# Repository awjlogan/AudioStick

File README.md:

# AudioStick

Quality audio carrier board for the Raspberry Pi Zero. A self facilitating media node.

## Description and Getting Started

This board is designed to be used with a Raspberry Pi Zero (W) to turn it into small high quality streaming audio device. It incorporates a soft power switch, which makes it easier to use in normal settings (e.g., don't need to SSH in to shutdown) and prolong the life of the SD card. The AudioStick connects directly to the standard Raspberry Pi 40pin GPIO header.

All design files and source code are under the [_Don't Be A Dick_][dbad-github] license.

### Installation on the Raspberry Pi

From a clean installation of Raspbian, log in to your Raspberry Pi and run the following 3 lines:

```shell
> sudo apt install git
> git clone https://github.com/awjlogan/audiostick.git
> cd ./audiostick
> sudo ./audiostick_setup.sh
```

The `audiostick_setup.sh` script will:
 - Install the PCM5102's configuration in the boot configuration
 - Add the `asound.conf` configuration file
 - Add the power control service
 - Shutdown the Raspberry Pi

When it is complete, you will need to remove and reconnect the power before powering on again.

### Using the AudioStick

 - When the AudioStick is off, there is no power supplied to the Raspberry Pi, so power consumption is minimised.
 - Pressing the button will power on the Raspberry Pi. The power LED will flash until the Raspberry Pi has successfully booted, at which point it will stay on.
 - To turn the AudioStick OFF, press and hold the button for at least one second. The power LED will flash until the Raspberry Pi has safely shutdown. Once the LED returns to pulsing, the Raspberry Pi is completely off and it is safe to remove the power if you wish.

### Raspberry Pi Setup

The AudioStick is intended to be used with something like MPD to allow you to connect up to any speaker (with amplifier) and get access to your local music or streaming services controlled by your phone. There are a lot of good tutorials (REVISIT add some links) available, so I won't reiterate the points here, but here are a few additional things that might be useful:

 - Change the Raspberry Pi's hostname to a meaningful name, for example `livingroompi`. This will also allow you to have multiple AudioSticks on the same network.
 - Configure your NAS (or whatever storage) to mount at boot time in `/etc/fstab`. Be aware that the system might attempt to mount the device before the network is available.
 - Disable the swap file to increase the SD card's life (`sudo apt remove dphys-swapfile`)

## Hardware

### PCB

The PCB was designed using [EAGLE][eagle-web] v9. The *.brd* and *.sch* files are provided, along with a small library of parts (*AudioStick.lbr*). A full bill of materials is provided as an *.ods* file.

### Firmware and flashing the ATtiny13A

The source for the power control microcontroller is provided, and can be compiled with the supplied Makefile. You will need to alter `Makefile` with the programmer that you are using. To compile the firmware:

`> /firmware/make`

The header **J4** on the PCB is a standard Microchip \[Atmel\] 6 pin programming header. Using your compiled firmware (or the precompiled *.hex* file), you can flash the microcontroller with e.g. an Atmel ICE. To flash the microcontroller, run:

`> /firmware/make flash`

## Change Notes

### Version 2.2

 - [x] -ELEC- Change from pogo pads to pin header for AVR ISP.

### Version 2.1

 - [x] -MECH- Mirror RasPi so connectors face Audiostick board.
 - [x] -ELEC- Move LED to PWM output pin for more interesting effects (chicken transistor in case programmer can't drive pin with LED).
 - [x] -ELEC- Remove MOSFET power switch for RasPi. Use inrush inhibitor instead.
 - [x] -ELEC- Downsize RasPi power capacitor.

### Version 2.0

Finalised release PCB, firmware, and RasPi software.

## Datasheets and useful links

- [PCM5102 DAC][pcm5102-datasheet]
- [ATtiny13A][attiny13-datasheet]

[dbad-github]: https://github.com/philsturgeon/dbad
[eagle-web]: https://www.autodesk.com/products/eagle/overview
[pcm5102-datasheet]: http://www.ti.com/product/PCM5102
[attiny13-datasheet]: https://www.microchip.com/wwwproducts/en/ATTINY13A

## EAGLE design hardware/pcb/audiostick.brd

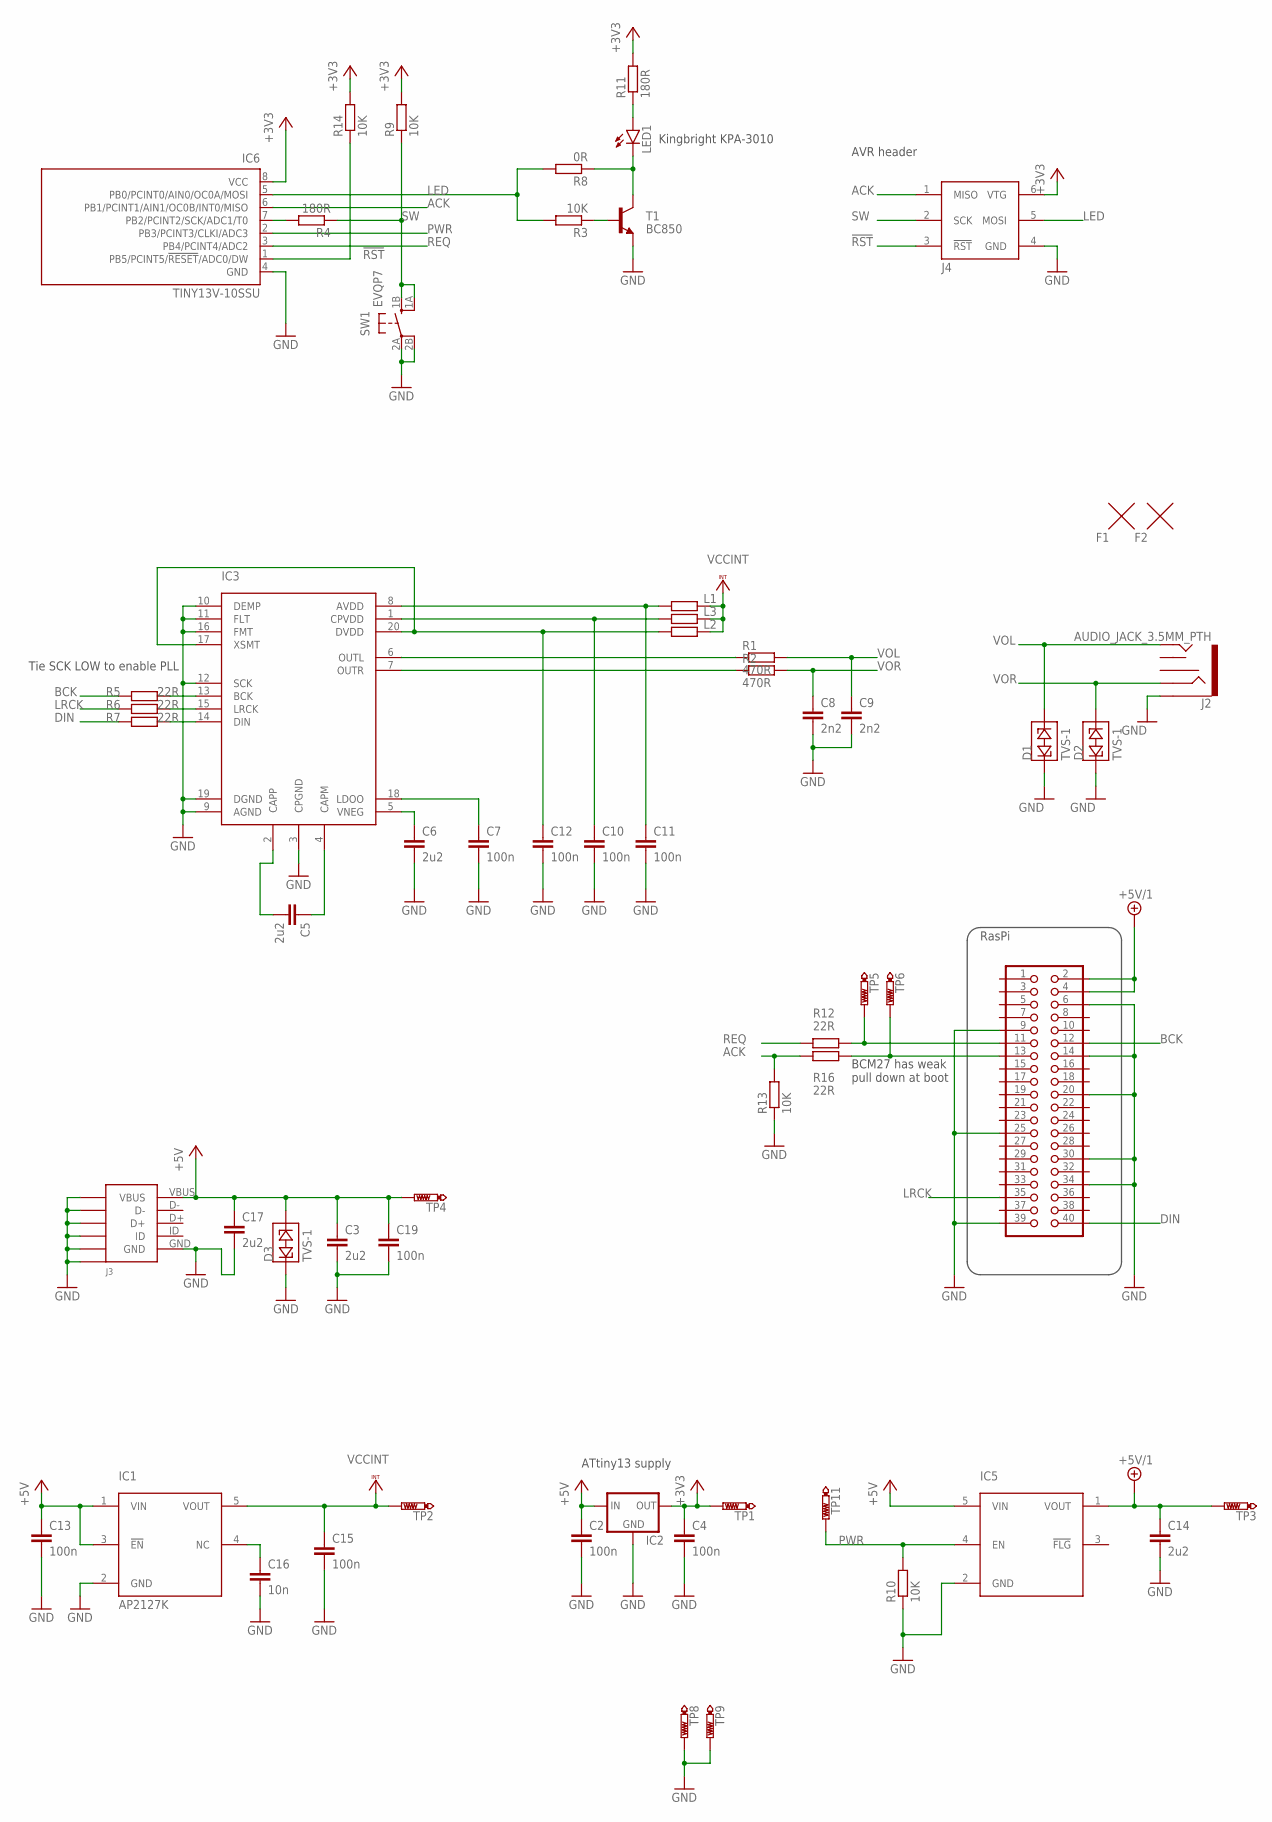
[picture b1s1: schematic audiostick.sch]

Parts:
C2, C4, C7, C10, C11, C12, C13, C15, C19: 100n; C0603
C3, C5, C6, C14, C17: 2u2; C0603
C8, C9: 2n2; C0603
C16: 10n; C0603
D1, D2, D3: TVS-1; R0603
F1, F2: FIDUCIALC2; CIRCLE-1MM-3R
IC1: AP2127K; GHI_SOT23-5
IC2: MCP1700TT; SOT-23
IC3: PCM5102ASW; TSSOP20
IC5: AP22804W5; GHI_SOT23-5
IC6: TINY13V-10SSU; 8S1
J2: AUDIO_JACK_3.5MM_PTH; AUDIO-JACK
J3: USB-B; 1050170001
J4: AVRISP; 2X3-1.27
L1, L2, L3: F; R0603
LED1: LEDLED; KPA-3010
R1, R2: 470R; R0603
R3, R9, R10, R13, R14: 10K; R0603
R4, R11: 180R; R0603
R5, R6, R7, R12, R16: 22R; R0603
R8: 0R; R0603
SW1: EVQP7; EVQP7L
T1: BC850; SOT23
TP1, TP2, TP3, TP4, TP5, TP6, TP8, TP9, TP11: PTR1PAD1-13; P1-13
U$1: RASPIZERO

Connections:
!RST: IC6.1 (PB5/PCINT5/!RESET!/ADC0/DW), J4.3 (!RST), R14.1
+3V3: C4.1, IC2.2 (OUT), IC6.8 (VCC), J4.6 (VTG), R9.2, R11.2, R14.2, TP1.TP
+5V: C2.1, C3.1, C13.1, C17.1, C19.1, D3.2 (3), IC1.1 (VIN), IC1.3 (!EN), IC2.3 (IN), IC5.5 (VIN), J3.VBUS, TP4.TP
+5V/1: C14.1, IC5.1 (VOUT), TP3.TP, U$1.2 (5V), U$1.4 (5V)
ACK: IC6.6 (PB1/PCINT1/AIN1/OC0B/INT0/MISO), J4.1 (MISO), R13.2, R16.1
ACK_IN: R16.2, TP6.TP, U$1.13 (27)
BCK: R5.1, U$1.12 (18)
DIN: R7.1, U$1.40 (21)
GND: C2.2, C3.2, C4.2, C6.2, C7.2, C8.2, C9.2, C10.2, C11.2, C12.2, C13.2, C14.2, C15.2, C16.2, C17.2, C19.2, D1.1, D2.1, D3.1, IC1.2 (GND), IC2.1 (GND), IC3.3 (CPGND), IC3.9 (AGND), IC3.10 (DEMP), IC3.11 (FLT), IC3.12 (SCK), IC3.16 (FMT), IC3.19 (DGND), IC5.2 (GND), IC6.4 (GND), J2.SLEEVE, J3.GND, J3.P$1 (SH1*4), J3.P$2 (SH1*1), J3.P$3 (SH1*2), J3.P$4 (SH1*3), J3.P$10 (SH1*5), J3.P$11 (SH1*6), J4.4 (GND), R10.1, R13.1, SW1.2A, SW1.2B (P1), T1.2 (E), TP8.TP, TP9.TP, U$1.6 (GND), U$1.9 (GND), U$1.14 (GND), U$1.20 (GND), U$1.25 (GND), U$1.30 (GND), U$1.34 (GND), U$1.39 (GND)
LED: IC6.5 (PB0/PCINT0/AIN0/OC0A/MOSI), J4.5 (MOSI), R3.2, R8.2
LRCK: R6.1, U$1.35 (19)
unnamed: C5.1, IC3.4 (CAPM)
unnamed: C5.2, IC3.2 (CAPP)
unnamed: C6.1, IC3.5 (VNEG)
unnamed: C7.1, IC3.18 (LDOO)
unnamed: IC3.6 (OUTL), R1.1
unnamed: R3.1, T1.1 (B)
unnamed: C11.1, IC3.8 (AVDD), L1.1
unnamed: IC3.7 (OUTR), R2.1
unnamed: IC3.13 (BCK), R5.2
unnamed: IC3.15 (LRCK), R6.2
unnamed: IC3.14 (DIN), R7.2
unnamed: C12.1, IC3.17 (XSMT), IC3.20 (DVDD), L2.1
unnamed: C10.1, IC3.1 (CPVDD), L3.1
unnamed: LED1.C, R8.1, T1.3 (C)
unnamed: C16.1, IC1.4 (NC)
unnamed: LED1.A, R11.1
unnamed: IC6.7 (PB2/PCINT2/SCK/ADC1/T0), R4.2
PWR: IC5.4 (EN), IC6.2 (PB3/PCINT3/CLKI/ADC3), R10.2, TP11.TP
REQ: IC6.3 (PB4/PCINT4/ADC2), R12.1
SW: J4.2 (SCK), R4.1, R9.1, SW1.1A (S1), SW1.1B (S)
S_REQ': R12.2, TP5.TP, U$1.11 (17)
VCCINT: C15.1, IC1.5 (VOUT), L1.2, L2.2, L3.2, TP2.TP
VOL: C9.1, D1.2 (3), J2.TIP, R1.2
VOR: C8.1, D2.2 (3), J2.RING, R2.2

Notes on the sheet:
Tie SCK LOW to enable PLL
BCM27 has weak pull down at boot
ATtiny13 supply
Kingbright KPA-3010
AVR header

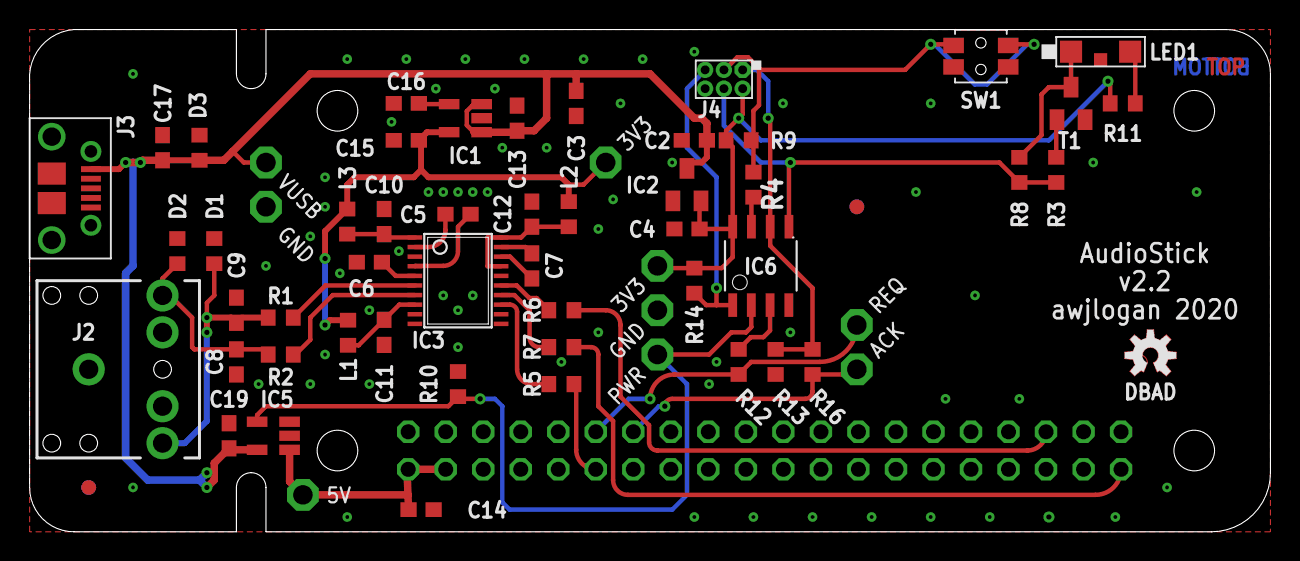
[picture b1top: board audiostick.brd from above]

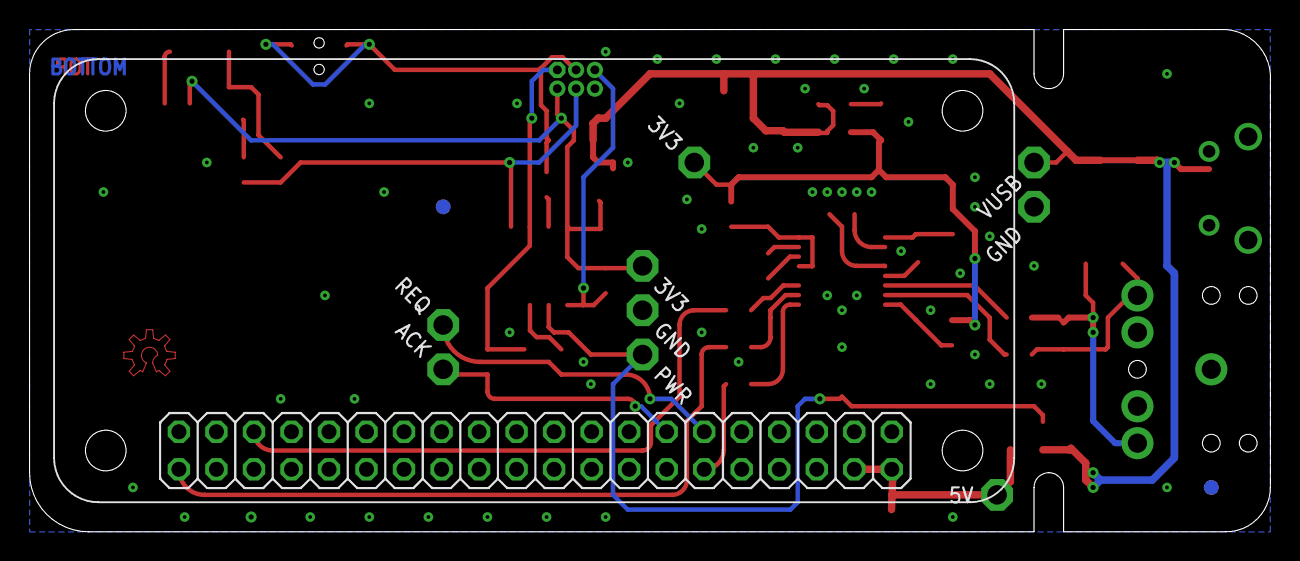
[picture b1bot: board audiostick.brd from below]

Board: 2 copper layers, 84.0 x 34.0 mm, 61 parts (2 on the bottom side), 35 nets.

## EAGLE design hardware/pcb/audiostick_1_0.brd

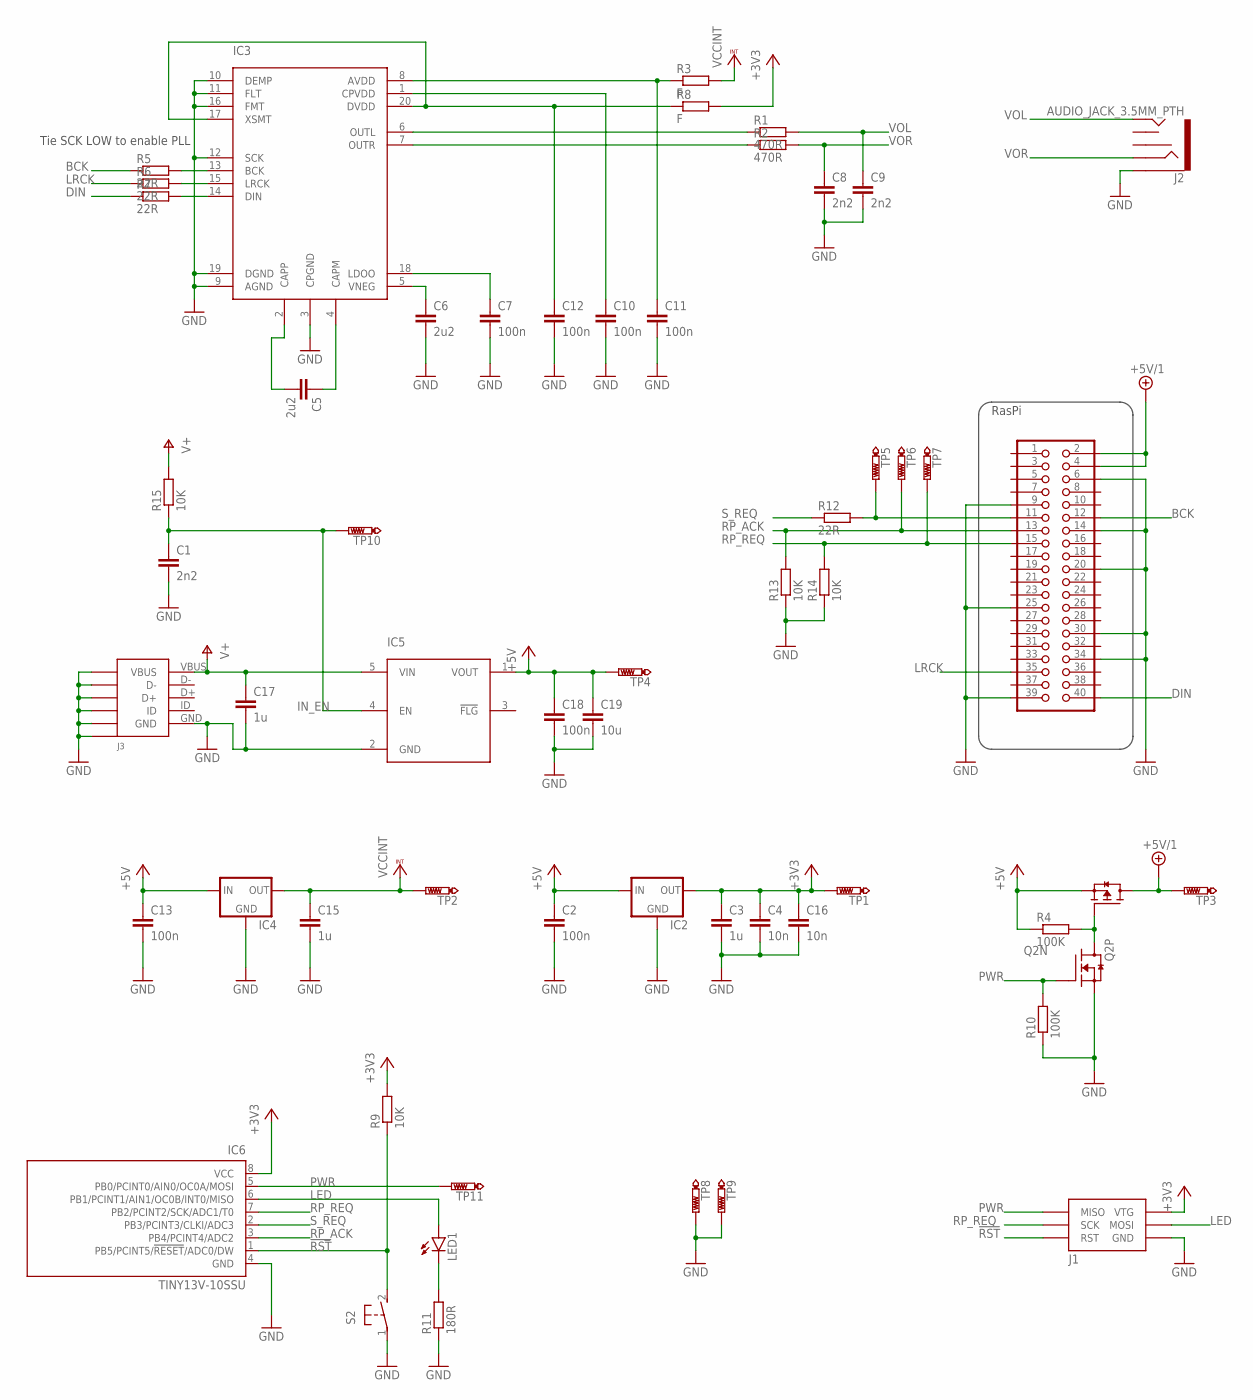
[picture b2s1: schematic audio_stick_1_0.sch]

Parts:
C1, C8, C9: 2n2; C0603
C2, C13: 100n; C0805
C3, C15, C17: 1u; C0805
C4, C16: 10n; C0805
C5, C6: 2u2; C0603
C7, C10, C11, C12, C18: 100n; C0603
C19: 10u; C0805
IC2, IC4: MCP1700TT; SOT-23
IC3: PCM5102ASW; TSSOP20
IC5: AP22804W5; GHI_SOT23-5
IC6: TINY13V-10SSU; 8S1
J1: AVRISP6TH127; 2X3-50MIL
J2: AUDIO_JACK_3.5MM_PTH; AUDIO-JACK
J3: USB-B; 1050170001
LED1: LED3MM
Q2: BSL215; 6TSOP
R1, R2: 470R; R0603
R3, R8: F; R0603
R4, R10: 100K; R0805
R5, R6, R7, R12: 22R; R0603
R9, R13, R14, R15: 10K; R0603
R11: 180R; R0805
S2: 31-XX; B3F-31XX
TP1, TP2, TP3, TP4, TP5, TP6, TP7, TP8, TP9, TP10, TP11: PTR1PAD1-13; P1-13
U$1: RASPIZERO

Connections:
!RST: IC6.1 (PB5/PCINT5/!RESET!/ADC0/DW), J1.5 (RST), R9.1, S2.2 (S)
+3V3: C3.1, C4.1, C16.1, IC2.2 (OUT), IC6.8 (VCC), J1.2 (VTG), R8.2, R9.2, TP1.TP
+5V: C2.1, C13.1, C18.1, C19.1, IC2.3 (IN), IC4.3 (IN), IC5.1 (VOUT), Q2.2 (S), R4.1, TP4.TP
+5V/1: Q2.4 (D), TP3.TP, U$1.2 (5V), U$1.4 (5V)
BCK: R5.1, U$1.12 (18)
DIN: R7.1, U$1.40 (21)
GND: C1.2, C2.2, C3.2, C4.2, C6.2, C7.2, C8.2, C9.2, C10.2, C11.2, C12.2, C13.2, C15.2, C16.2, C17.2, C18.2, C19.2, IC2.1 (GND), IC3.3 (CPGND), IC3.9 (AGND), IC3.10 (DEMP), IC3.11 (FLT), IC3.12 (SCK), IC3.16 (FMT), IC3.19 (DGND), IC4.1 (GND), IC5.2 (GND), IC6.4 (GND), J1.6 (GND), J2.SLEEVE, J3.GND, J3.P$1 (SH1*4), J3.P$2 (SH1*1), J3.P$3 (SH1*2), J3.P$4 (SH1*3), J3.P$10 (SH1*5), J3.P$11 (SH1*6), Q2.5 (S), R10.1, R11.1, R13.1, R14.1, S2.1, TP8.TP, TP9.TP, U$1.6 (GND), U$1.9 (GND), U$1.14 (GND), U$1.20 (GND), U$1.25 (GND), U$1.30 (GND), U$1.34 (GND), U$1.39 (GND)
IN_EN: C1.1, IC5.4 (EN), R15.1, TP10.TP
LED: IC6.6 (PB1/PCINT1/AIN1/OC0B/INT0/MISO), J1.4 (MOSI), LED1.A
LRCK: R6.1, U$1.35 (19)
unnamed: C5.1, IC3.4 (CAPM)
unnamed: C5.2, IC3.2 (CAPP)
unnamed: C6.1, IC3.5 (VNEG)
unnamed: C7.1, IC3.18 (LDOO)
unnamed: IC3.6 (OUTL), R1.1
unnamed: Q2.3 (G), Q2.6 (D), R4.2
unnamed: C10.1, IC3.1 (CPVDD)
unnamed: IC3.7 (OUTR), R2.1
unnamed: IC3.13 (BCK), R5.2
unnamed: IC3.15 (LRCK), R6.2
unnamed: IC3.14 (DIN), R7.2
unnamed: C12.1, IC3.17 (XSMT), IC3.20 (DVDD), R8.1
unnamed: C11.1, IC3.8 (AVDD), R3.1
unnamed: LED1.K (C), R11.2
PWR: IC6.5 (PB0/PCINT0/AIN0/OC0A/MOSI), J1.1 (MISO), Q2.1 (G), R10.2, TP11.TP
RP_ACK: IC6.3 (PB4/PCINT4/ADC2), R13.2, TP6.TP, U$1.13 (27)
RP_REQ: IC6.7 (PB2/PCINT2/SCK/ADC1/T0), J1.3 (SCK), R14.2, TP7.TP, U$1.15 (22)
S_REQ: IC6.2 (PB3/PCINT3/CLKI/ADC3), R12.1
S_REQ': R12.2, TP5.TP, U$1.11 (17)
V+: C17.1, IC5.5 (VIN), J3.VBUS, R15.2
VCCINT: C15.1, IC4.2 (OUT), R3.2, TP2.TP
VOL: C9.1, J2.TIP, R1.2
VOR: C8.1, J2.RING, R2.2

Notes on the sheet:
Tie SCK LOW to enable PLL

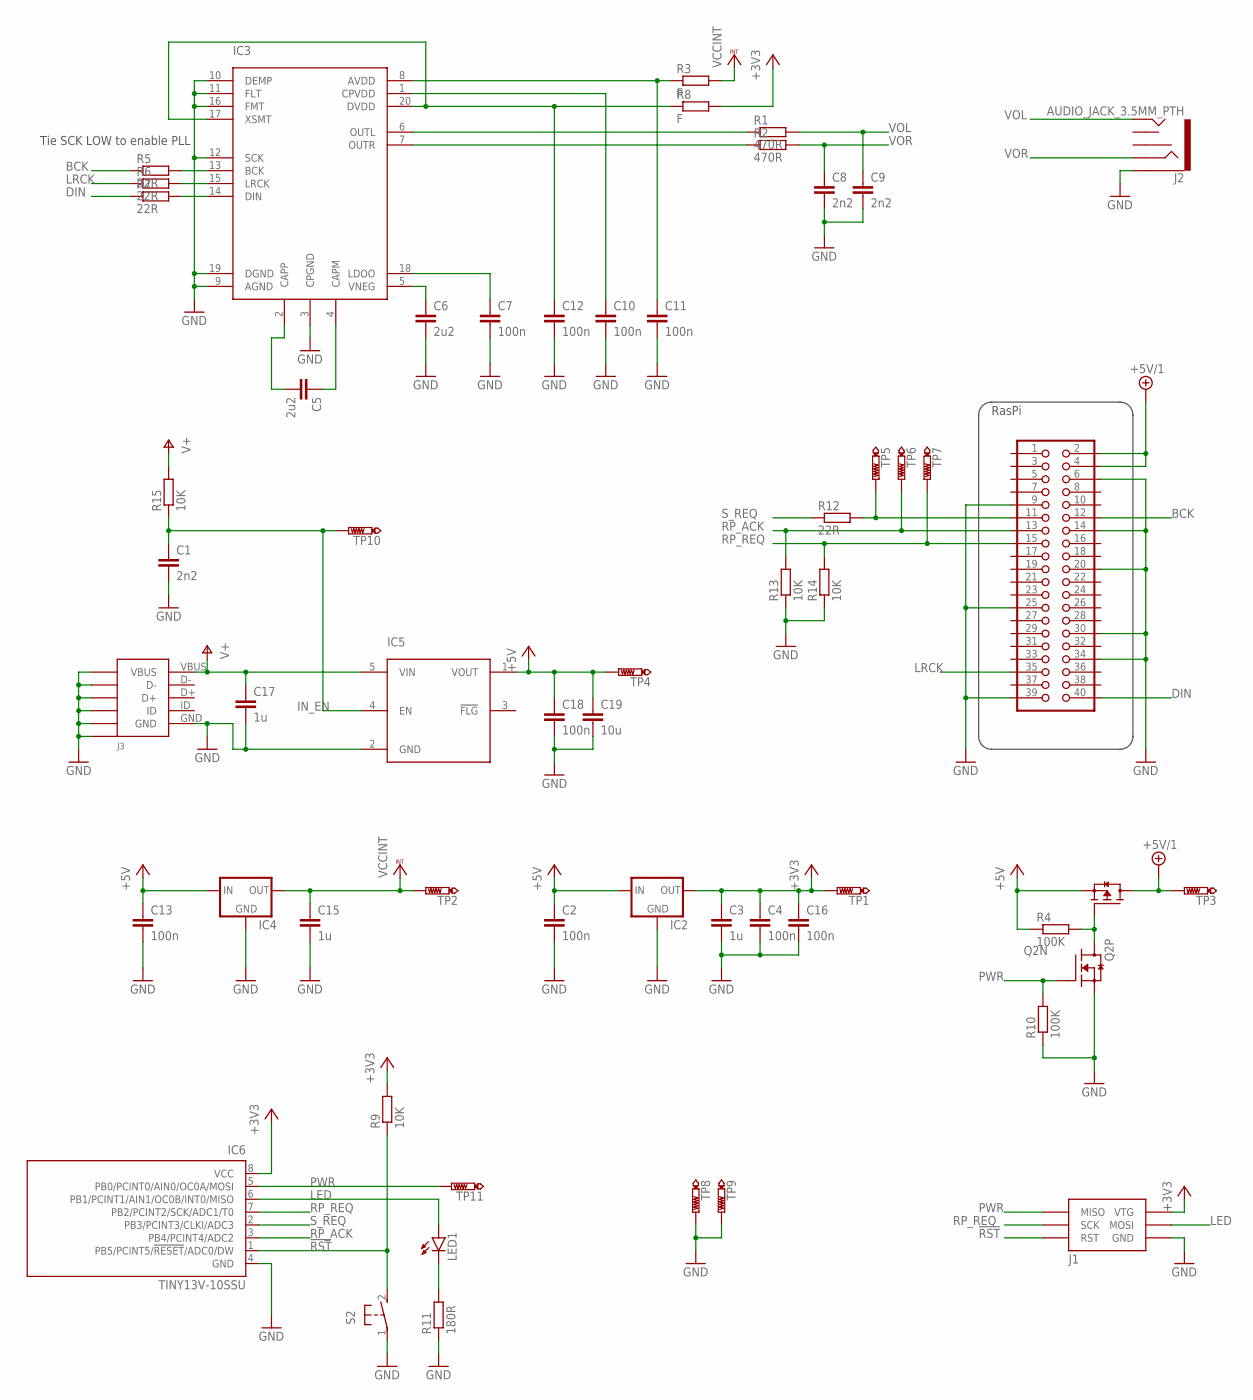
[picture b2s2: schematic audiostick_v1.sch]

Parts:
C1, C8, C9: 2n2; C0603
C2, C4, C13, C16: 100n; C0805
C3, C15, C17: 1u; C0805
C5, C6: 2u2; C0603
C7, C10, C11, C12, C18: 100n; C0603
C19: 10u; C0805
IC2, IC4: MCP1700TT; SOT-23
IC3: PCM5102ASW; TSSOP20
IC5: AP22804W5; GHI_SOT23-5
IC6: TINY13V-10SSU; 8S1
J1: AVRISP6TH127; 2X3-50MIL
J2: AUDIO_JACK_3.5MM_PTH; AUDIO-JACK
J3: USB-B; 1050170001
LED1: LED3MM
Q2: BSL215; 6TSOP
R1, R2: 470R; R0603
R3, R8: F; R0603
R4, R10: 100K; R0805
R5, R6, R7, R12: 22R; R0603
R9, R13, R14, R15: 10K; R0603
R11: 180R; R0805
S2: 31-XX; B3F-31XX
TP1, TP2, TP3, TP4, TP5, TP6, TP7, TP8, TP9, TP10, TP11: PTR1PAD1-13; P1-13
U$1: RASPIZERO

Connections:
!RST: IC6.1 (PB5/PCINT5/!RESET!/ADC0/DW), J1.5 (RST), R9.1, S2.2 (S)
+3V3: C3.1, C4.1, C16.1, IC2.2 (OUT), IC6.8 (VCC), J1.2 (VTG), R8.2, R9.2, TP1.TP
+5V: C2.1, C13.1, C18.1, C19.1, IC2.3 (IN), IC4.3 (IN), IC5.1 (VOUT), Q2.2 (S), R4.1, TP4.TP
+5V/1: Q2.4 (D), TP3.TP, U$1.2 (5V), U$1.4 (5V)
BCK: R5.1, U$1.12 (18)
DIN: R7.1, U$1.40 (21)
GND: C1.2, C2.2, C3.2, C4.2, C6.2, C7.2, C8.2, C9.2, C10.2, C11.2, C12.2, C13.2, C15.2, C16.2, C17.2, C18.2, C19.2, IC2.1 (GND), IC3.3 (CPGND), IC3.9 (AGND), IC3.10 (DEMP), IC3.11 (FLT), IC3.12 (SCK), IC3.16 (FMT), IC3.19 (DGND), IC4.1 (GND), IC5.2 (GND), IC6.4 (GND), J1.6 (GND), J2.SLEEVE, J3.GND, J3.P$1 (SH1*4), J3.P$2 (SH1*1), J3.P$3 (SH1*2), J3.P$4 (SH1*3), J3.P$10 (SH1*5), J3.P$11 (SH1*6), Q2.5 (S), R10.1, R11.1, R13.1, R14.1, S2.1, TP8.TP, TP9.TP, U$1.6 (GND), U$1.9 (GND), U$1.14 (GND), U$1.20 (GND), U$1.25 (GND), U$1.30 (GND), U$1.34 (GND), U$1.39 (GND)
IN_EN: C1.1, IC5.4 (EN), R15.1, TP10.TP
LED: IC6.6 (PB1/PCINT1/AIN1/OC0B/INT0/MISO), J1.4 (MOSI), LED1.A
LRCK: R6.1, U$1.35 (19)
unnamed: C5.1, IC3.4 (CAPM)
unnamed: C5.2, IC3.2 (CAPP)
unnamed: C6.1, IC3.5 (VNEG)
unnamed: C7.1, IC3.18 (LDOO)
unnamed: IC3.6 (OUTL), R1.1
unnamed: Q2.3 (G), Q2.6 (D), R4.2
unnamed: C10.1, IC3.1 (CPVDD)
unnamed: IC3.7 (OUTR), R2.1
unnamed: IC3.13 (BCK), R5.2
unnamed: IC3.15 (LRCK), R6.2
unnamed: IC3.14 (DIN), R7.2
unnamed: C12.1, IC3.17 (XSMT), IC3.20 (DVDD), R8.1
unnamed: C11.1, IC3.8 (AVDD), R3.1
unnamed: LED1.K (C), R11.2
PWR: IC6.5 (PB0/PCINT0/AIN0/OC0A/MOSI), J1.1 (MISO), Q2.1 (G), R10.2, TP11.TP
RP_ACK: IC6.3 (PB4/PCINT4/ADC2), R13.2, TP6.TP, U$1.13 (27)
RP_REQ: IC6.7 (PB2/PCINT2/SCK/ADC1/T0), J1.3 (SCK), R14.2, TP7.TP, U$1.15 (22)
S_REQ: IC6.2 (PB3/PCINT3/CLKI/ADC3), R12.1
S_REQ': R12.2, TP5.TP, U$1.11 (17)
V+: C17.1, IC5.5 (VIN), J3.VBUS, R15.2
VCCINT: C15.1, IC4.2 (OUT), R3.2, TP2.TP
VOL: C9.1, J2.TIP, R1.2
VOR: C8.1, J2.RING, R2.2

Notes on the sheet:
Tie SCK LOW to enable PLL

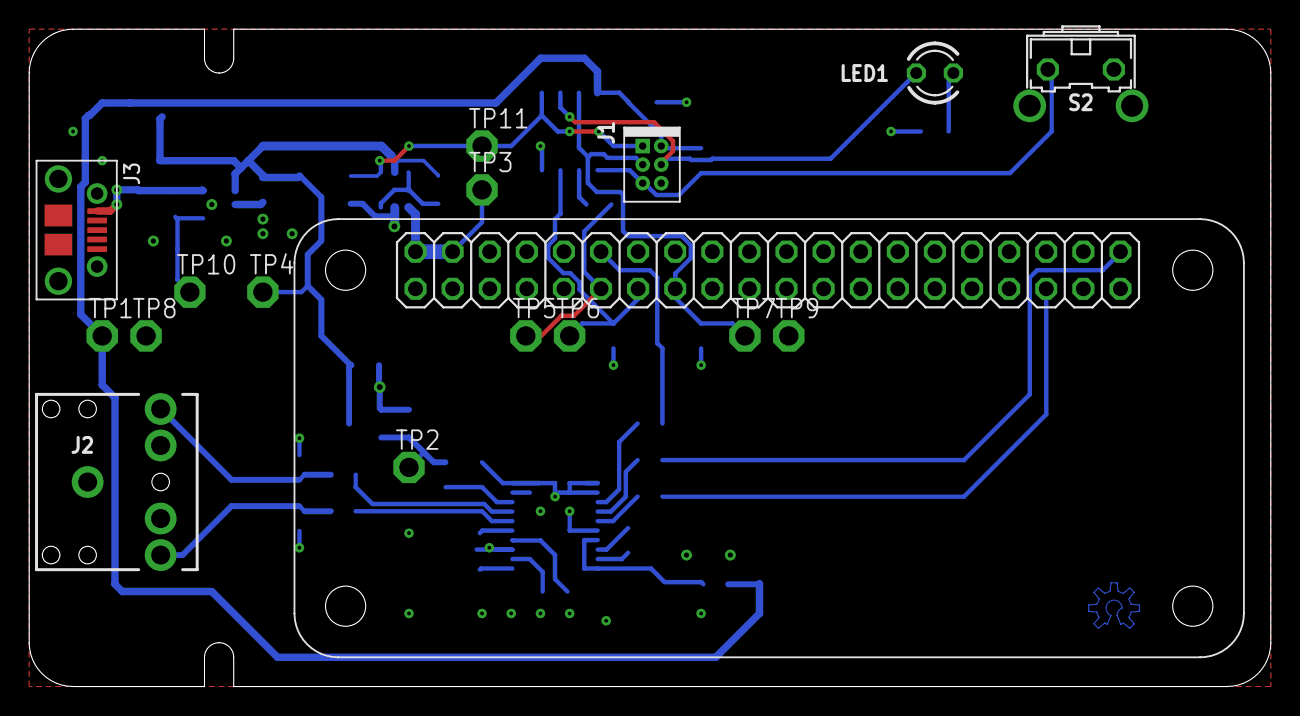
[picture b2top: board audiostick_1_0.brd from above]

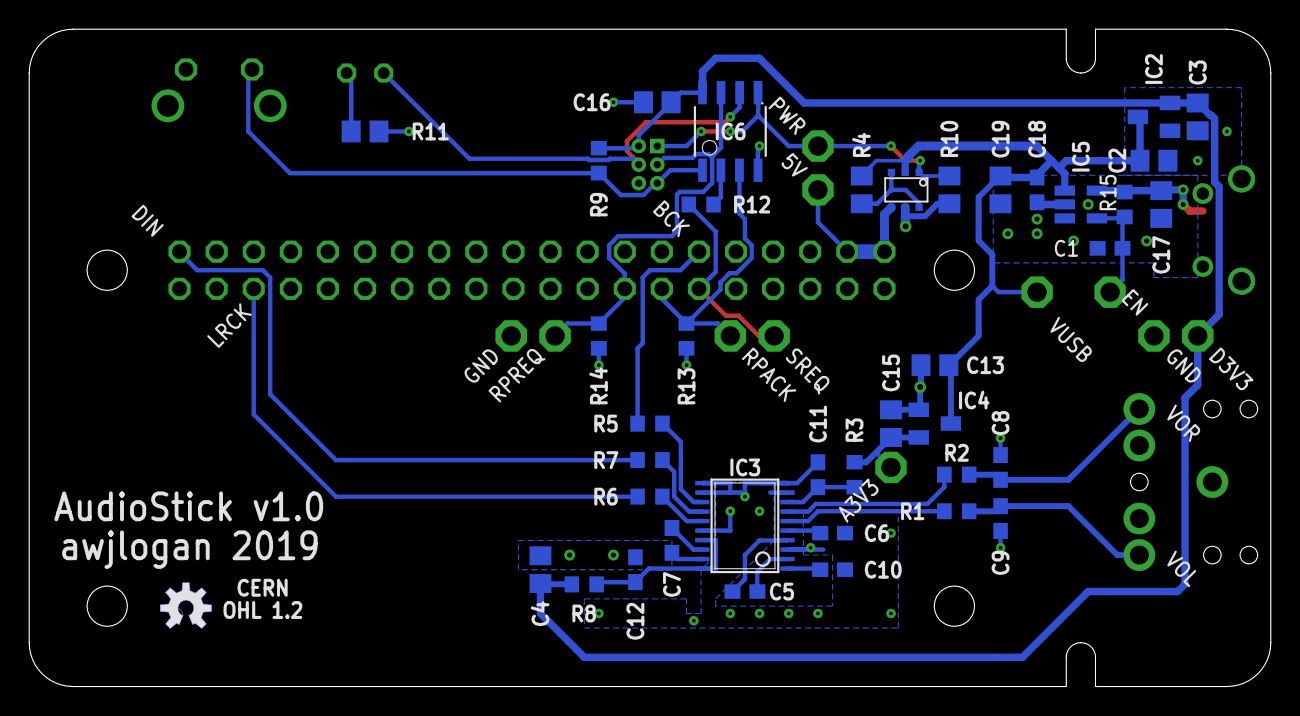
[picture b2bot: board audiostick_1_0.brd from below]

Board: 2 copper layers, 85.0 x 45.0 mm, 56 parts (39 on the bottom side), 33 nets.

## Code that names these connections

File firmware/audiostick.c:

/*

Copyright 2019 Angus Logan

Permission is hereby granted, free of charge, to any person obtaining a copy of
this software and associated documentation files (the "Software"), to deal in
the Software without restriction, including without limitation the rights to
use, copy, modify, merge, publish, distribute, sublicense, and/or sell copies
of the Software, and to permit persons to whom the Software is furnished to
do so, subject to the following conditions:

The above copyright notice and this permission notice shall be included in all
copies or substantial portions of the Software.

THE SOFTWARE IS PROVIDED "AS IS", WITHOUT WARRANTY OF ANY KIND, EXPRESS OR
IMPLIED, INCLUDING BUT NOT LIMITED TO THE WARRANTIES OF MERCHANTABILITY,
FITNESS FOR A PARTICULAR PURPOSE AND NONINFRINGEMENT. IN NO EVENT SHALL THE
AUTHORS OR COPYRIGHT HOLDERS BE LIABLE FOR ANY CLAIM, DAMAGES OR OTHER
LIABILITY, WHETHER IN AN ACTION OF CONTRACT, TORT OR OTHERWISE, ARISING FROM,
OUT OF OR IN CONNECTION WITH THE SOFTWARE OR THE USE OR OTHER DEALINGS IN THE
SOFTWARE.

 * Author:  Angus Logan
 * Version: 2.0
 * Date:    January 2020
 * Target:  Microchip [Atmel] ATtiny13A
 *
 * Physical <-> logical pin mapping
 *
 * Package: SOIC8/DIP8
 * Physical     Function        Logical     i/o
 *----------------------------------------------
 *  1           !RST            PB5         -
 *  2           PWR             PB3         o
 *  3           LED             PB4         o
 *  4           < GND >                     -
 *  5           REQ             PB0         o
 *  6           ACK             PB1         i
 *  7           SW              PB2         i
 *  8           < VDD >                     -
 *
 */

#include <avr/io.h>
#include <avr/interrupt.h>
#include <avr/sleep.h>

#include "audiostick.h"

static inline void setup(void);

ISR (TIM0_OVF_vect) {
    // Reset for idle interrupt wakeup
    TCNT0 = TMR0_VAL;
}

int main(void)
{
    /* Switch handler */
    const uint8_t SW_OPEN = 0xFFU; // Switch goes to ground
    const uint8_t SW_CLOSED = 0x0U;
    uint8_t sw_state = SW_OPEN;
    sw_t sw_curr = OPEN;
    sw_t sw_last = OPEN;
    uint8_t was_pressed = 0x0U;

    /* Timers */
    uint16_t rst_assert = 0x0U;  // timer for reset button
    uint16_t wdt_assert = 0x0U;  // timer to catch a hang in a state
    uint8_t wdt_overflow = 0x0U;

    /*  FSM
        From cold power on, start in ON - no software required on RPi
    */
    power_fsm_t power_fsm = ON;
    power_fsm_t power_fsm_nxt = ON;
    uint8_t rp_ack = 0x0U;

    /* Driven outputs */
    uint8_t portb_nxt;
    uint8_t flash_val = NORM_VAL;
    uint8_t flash_count = 0x0U;

    /* Forever */
    setup();

    for (;;) {

        /* Debounce switch
           Shift all left, then add current to LSB
            -> compare again CLOSED/OPEN (depending on pullup/down)
        */
        sw_state <<= 1;
        if (PINB & (1U<<SW)) sw_state++;
        if (sw_state == SW_CLOSED) sw_curr = CLOSED;
        else if (sw_state == SW_OPEN) sw_curr = OPEN;

        /* Reused conditions */
        was_pressed = (sw_curr == CLOSED) && (sw_last == OPEN);
        wdt_overflow = (wdt_assert > TIMEOUT_VAL);
        rp_ack = (PINB & (1U<<ACK));

        // update FSM
        switch (power_fsm) {
        case OFF:
            if (was_pressed) power_fsm_nxt = START_REQ;
            break;
        case START_REQ:
            if (wdt_overflow) power_fsm_nxt = ERROR;
            else if (rp_ack) power_fsm_nxt = START_ACK;
            break;
        case START_ACK:
            if (wdt_overflow) power_fsm_nxt = ERROR;
            else if (!rp_ack) power_fsm_nxt = ON;
            break;
        case ON:
            if (was_pressed) power_fsm_nxt = SHUT_REQ;
            // request to shutdown from RPi
            else if (PINB & (1U<<REQ)) power_fsm_nxt = SHUT_REQ;
            break;
        case SHUT_REQ:
            if (wdt_overflow) power_fsm_nxt = ERROR;
            else if (rp_ack) power_fsm_nxt = SHUT_ACK;
            break;
        case SHUT_ACK:
            if (wdt_overflow) power_fsm_nxt = ERROR;
            else if (!rp_ack) power_fsm_nxt = OFF;
            break;
        case ERROR:
            break;
        }

        /* Update the watchdog timer */
        if (power_fsm != power_fsm_nxt) wdt_assert = 0x0U;
        else wdt_assert++;

        /* Check for reset */
        if ((sw_curr == CLOSED) && (sw_last == CLOSED)) rst_assert++;
        else rst_assert = 0x0U;
        if (rst_assert > RST_VAL) power_fsm_nxt = OFF;

        // Update FSM state
        power_fsm = power_fsm_nxt;
        sw_last = sw_curr;

        /* Drive FSM outputs */
        portb_nxt = PORTB;

        // Flash by default, exceptions ON/OFF are handled in FSM
        flash_count++;
        if (flash_count > flash_val) {
            portb_nxt ^= (1U<<LED);
            flash_count = 0x0U;
        }

        switch (power_fsm) {
        case OFF:
            flash_val = NORM_VAL;
            portb_nxt &= ~(1U<<LED) & ~(1U<<PWR);  // LED & power off
            break;
        case START_REQ:
            portb_nxt |= (1U<<PWR) | (1U<<REQ);  // power on and assert REQ
            break;
        case START_ACK:
            portb_nxt &= ~(1U<<REQ);  // Clear REQ
            break;
        case ON:
            portb_nxt |= (1U<<LED);  // LED on
            break;
        case SHUT_REQ:
            portb_nxt |= (1U<<REQ);  // Assert REQ
            break;
        case SHUT_ACK:
            portb_nxt &= ~(1U<<REQ);  // Clear REQ
            break;
        case ERROR:
            flash_val = ERR_VAL;
            break;
        }
        PORTB = portb_nxt;

        // Sleep and wait for timer0 interrupt
        sleep_enable();
        sleep_cpu();
        sleep_disable();
    }
}

static inline void setup(void) {
    /* Clocking: default */
    /* Interrupts: default */

    /* Timer0 */
    /* Overflow every INT_PER ms */
    TCCR0B = (1U<<CS01) | (1U<<CS00);  // clk / 64
    TIMSK0 = (1U<<TOIE0);

    /* Port B: */
    MCUCR = (1U<<PUD);  // disable pull ups
    // Configure outputs
    DDRB = (1U<<DDB0) | (1U<<DDB3) | (1U<<DDB4);

    /* Power reduction */
    PRR = (1U<<PRADC);  // ADC off
    ACSR = (1U<<ACD);  // analog comparator off
}

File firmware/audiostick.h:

/*

Copyright 2019 Angus Logan

Permission is hereby granted, free of charge, to any person obtaining a copy of
this software and associated documentation files (the "Software"), to deal in
the Software without restriction, including without limitation the rights to
use, copy, modify, merge, publish, distribute, sublicense, and/or sell copies
of the Software, and to permit persons to whom the Software is furnished to
do so, subject to the following conditions:

The above copyright notice and this permission notice shall be included in all
copies or substantial portions of the Software.

THE SOFTWARE IS PROVIDED "AS IS", WITHOUT WARRANTY OF ANY KIND, EXPRESS OR
IMPLIED, INCLUDING BUT NOT LIMITED TO THE WARRANTIES OF MERCHANTABILITY,
FITNESS FOR A PARTICULAR PURPOSE AND NONINFRINGEMENT. IN NO EVENT SHALL THE
AUTHORS OR COPYRIGHT HOLDERS BE LIABLE FOR ANY CLAIM, DAMAGES OR OTHER
LIABILITY, WHETHER IN AN ACTION OF CONTRACT, TORT OR OTHERWISE, ARISING FROM,
OUT OF OR IN CONNECTION WITH THE SOFTWARE OR THE USE OR OTHER DEALINGS IN THE
SOFTWARE.

*/

#ifndef AUDIOSTICK_H_
#define AUDIOSTICK_H_

// Pin assignments
#define SW      5
#define RP_ACK  4
#define S_REQ   3
#define RP_REQ  2
#define LED     1
#define PWR     0

// Time related defines
#define F_CPU       1200UL                                  /* Default clocking: 9.6 MHz / 8 (kHz) */
#define CLK_DIV     64U                                     /* TMR0 clock divider from F_CPU */
#define INT_PER     8U                                      /* Time between wakeups (ms) */
#define TMR0_VAL    (255U - (F_CPU * INT_PER / CLK_DIV))    /* Value to reset TMR0 */
#define NORM_PER    500UL                                   /* Normal flashing period (ms) */
#define NORM_VAL    NORM_PER / INT_PER                      /* Compare value */
#define ERR_PER     250U                                    /* Error flashing period (ms) */
#define ERR_VAL     ERR_PER / INT_PER                       /* Compare value */
#define RST_PER     2500UL                                  /* Time to hold for reset */
#define RST_VAL     RST_PER / INT_PER                       /* Compare value */
#define TIMEOUT_PER 32000UL                                 /* Error time out (ms) */
#define TIMEOUT_VAL TIMEOUT_PER / INT_PER                   /* Compare value */

// Power states
typedef enum {
    OFF,
    START_REQ,
    START_ACK,
    ON,
    SHUT_REQ,
    SHUT_ACK,
    ERROR
} power_fsm_t;

// Button states
typedef enum {
    OPEN,
    CLOSED
} sw_t;

#endif /* AUDIOSTICK_H_ */

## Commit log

2019-06-14 First commit of project files
    README to be updated.
2019-08-12 Added (untested) Pi side scripts
2019-10-13 Added initial BOM, update of README, added Makefile STILL NOT TESTED!
2020-01-04 first v2 commit
2020-01-13 v2.0 changes
2020-01-13 Resolve symlink
2020-01-16 Complete revision of design - layout, connections, parts. Ready for proto run
2020-01-16 Moved text slightly
2020-01-16 Change license to DBAD
2020-01-16 Rename LICENSE to LICENSE.md
2020-01-16 Rearrange folders
2020-01-20 Final revision before manufacture
2020-01-22 Moved vias for standoffs
2020-03-16 Update BOM, start updating readme
2020-03-23 Minimum software support
2020-03-26 Some PWM effect playing
2020-04-14 Start of v3 port to KiCad
2020-04-15 Changes made
2020-04-15 Working ON/OFF mechanism
2020-04-16 Added wait states, not yet working
2020-04-17 Fix short exit from STOP_WAIT state - overflow error
2020-04-18 chmod for mds, add laser cut path
2020-04-20 Changes to setup scripts and RasPi power service
2020-04-20 Update Pi side scripts and setup
2020-04-20 Less delay needed for STOP_WAIT state
2020-04-21 Unstash changes for v3
2020-04-21 Removed old Eagle files for v3
2020-04-22 Started layout - will need to mirror RasPi connector
2020-04-23 Update of README and setup script
2020-05-03 More layout; BOM rationalisation
2020-05-04 More layout
2020-05-04 Finish preliminary layout
2020-05-04 Change EEPROM and more layout revision
2020-05-11 Start test plan and jig
2020-05-11 Removed external EEPROM, some layout changes
2020-08-11 Added rendered schematic
2020-08-31 2.0 -> 2.1 simplification, PCB rearrangement
2020-08-31 Complete rewrite start
2020-09-01 Change switch
2020-09-01 Fix airwire and clearance
2020-09-02 Refactoring of ATtiny code; update of README.md
2020-09-02 Rationalised BOM a little
2020-09-02 Update BOM
2020-09-09 Revert to EVQ switch
2020-09-09 Change switch in BOM
2020-09-14 sync to remote
2020-11-23 Update board, BOM, and firmware
2020-12-29 Fixed RasPi setup script and README
2021-01-15 Remove unused STOP_WAIT state
2021-02-15 Real HW in hand
2021-02-15 Changed pogo points for proper header, silly idea!
2021-02-16 Confirm LED pulse working
2021-02-28 Finish schematic/layout changes
2021-02-28 Adding LED pulse effect
2021-02-28 Update README and Eagle lib
2021-05-20 * Add case STLs
2021-11-02 Disable default sound driver
2022-10-01 - install git as first step
2022-10-01 Remove redundant setup information

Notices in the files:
parts and their libraries:
SparkFun-Connectors: Licensing: Creative Commons ShareAlike 4.0 International - https://creativecommons.org/licenses/by-sa/4.0
